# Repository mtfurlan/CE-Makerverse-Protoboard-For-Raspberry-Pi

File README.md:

# Protoboard For Raspberry Pi

Based on the one by CE, modified to include an eeprom from [Adafruit](https://github.com/adafruit/Adafruit-Perma-Proto-HAT-PCB) as example

Not finished, I got distracted and then stoppped needing this

## See also
* [RPI HAT spec](https://github.com/raspberrypi/utils/tree/master/eeptools)

## License
This project is open source - please review the LICENSE.md file for further licensing information.

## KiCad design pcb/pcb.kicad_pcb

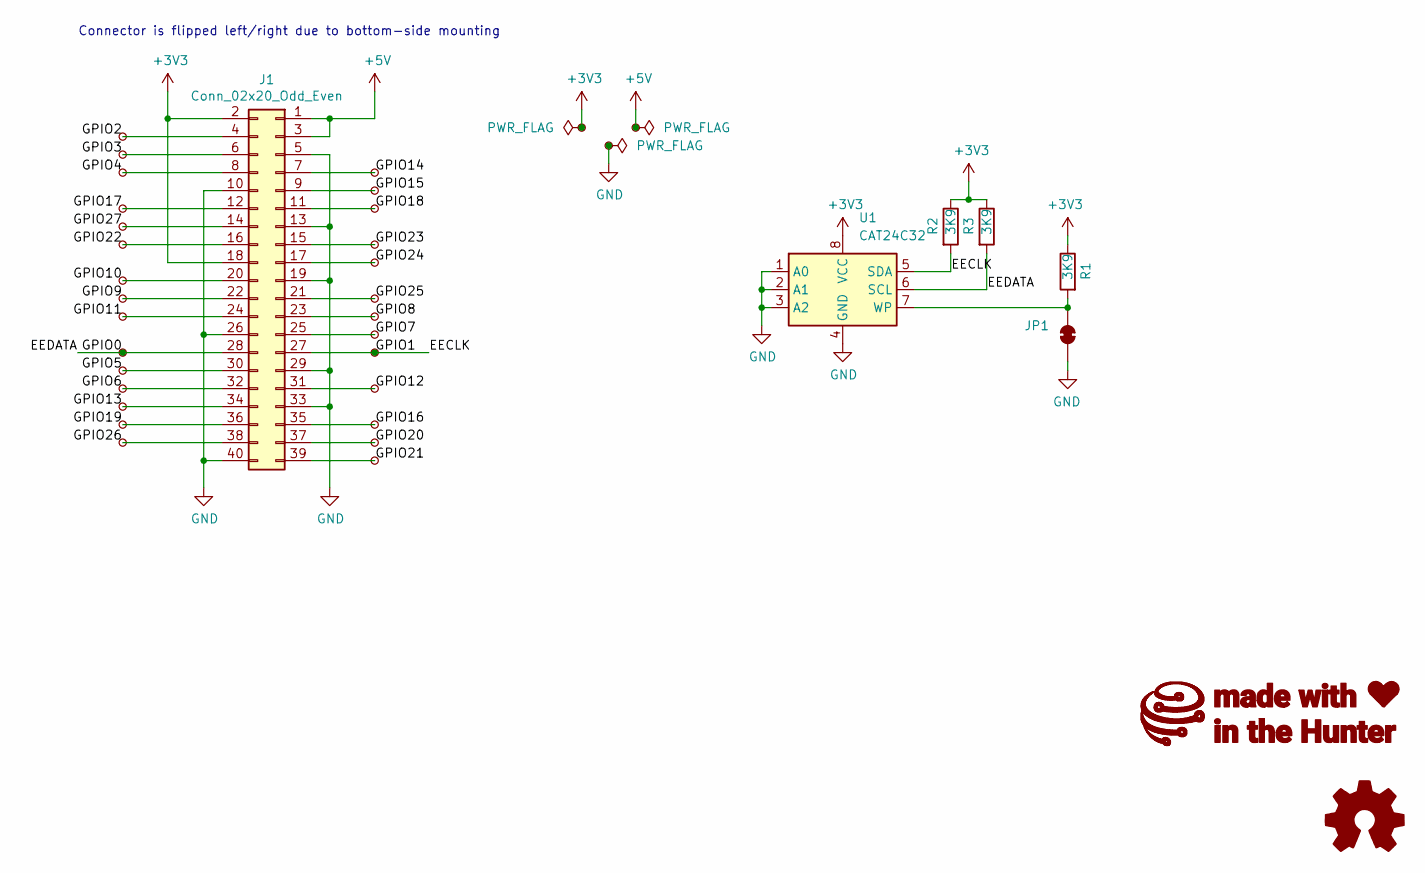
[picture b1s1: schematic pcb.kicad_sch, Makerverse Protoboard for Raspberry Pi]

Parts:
J1: Conn_02x20_Odd_Even; PinHeader_2x20_P2.54mm_Vertical
JP1: SolderJumper_2_Bridged; SolderJumper-2_P1.3mm_Bridged_RoundedPad1.0x1.5mm
LOGO1: Logo_Open_Hardware_Small; oshw
R1, R2, R3: 3K9; R_0603_1608Metric_Pad0.98x0.95mm_HandSolder
TP1, TP2, TP3, TP4, TP5, TP6, TP7, TP8, TP9, TP10, TP11, TP12, TP13, TP14, TP15, TP16, TP17, TP18, TP19, TP20, TP21, TP22, TP23, TP24, TP25, TP26, TP27, TP28: TestPoint_Small; 2-pin-row
TP29, TP31: TestPoint_Small; 4-pin-row
TP30: TestPoint_Small; BusRail-18-Hole
U1: CAT24C32; SOIC-8_3.9x4.9mm_P1.27mm

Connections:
+3V3: J1.2, J1.18, R1.1, R2.1, R3.1, TP29.1, U1.8 (VCC)
+5V: J1.1, J1.3, TP31.1
/EECLK: J1.27, R2.2, TP9.1, U1.5 (SDA)
/EEDATA: J1.28, R3.2, TP23.1, U1.6 (SCL)
/GPIO2: J1.4, TP14.1
/GPIO3: J1.6, TP15.1
/GPIO4: J1.8, TP16.1
/GPIO5: J1.30, TP24.1
/GPIO6: J1.32, TP25.1
/GPIO7: J1.25, TP8.1
/GPIO8: J1.23, TP7.1
/GPIO9: J1.22, TP21.1
/GPIO10: J1.20, TP20.1
/GPIO11: J1.24, TP22.1
/GPIO12: J1.31, TP10.1
/GPIO13: J1.34, TP26.1
/GPIO14: J1.7, TP1.1
/GPIO15: J1.9, TP2.1
/GPIO16: J1.35, TP11.1
/GPIO17: J1.12, TP17.1
/GPIO18: J1.11, TP3.1
/GPIO19: J1.36, TP27.1
/GPIO20: J1.37, TP12.1
/GPIO21: J1.39, TP13.1
/GPIO22: J1.16, TP19.1
/GPIO23: J1.15, TP4.1
/GPIO24: J1.17, TP5.1
/GPIO25: J1.21, TP6.1
/GPIO26: J1.38, TP28.1
/GPIO27: J1.14, TP18.1
GND: J1.5, J1.10, J1.13, J1.19, J1.26, J1.29, J1.33, J1.40, JP1.2 (B), TP30.1, U1.1 (A0), U1.2 (A1), U1.3 (A2), U1.4 (GND)
unnamed: JP1.1 (A), R1.2, U1.7 (WP)

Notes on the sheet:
Connector is flipped left/right due to bottom-side mounting

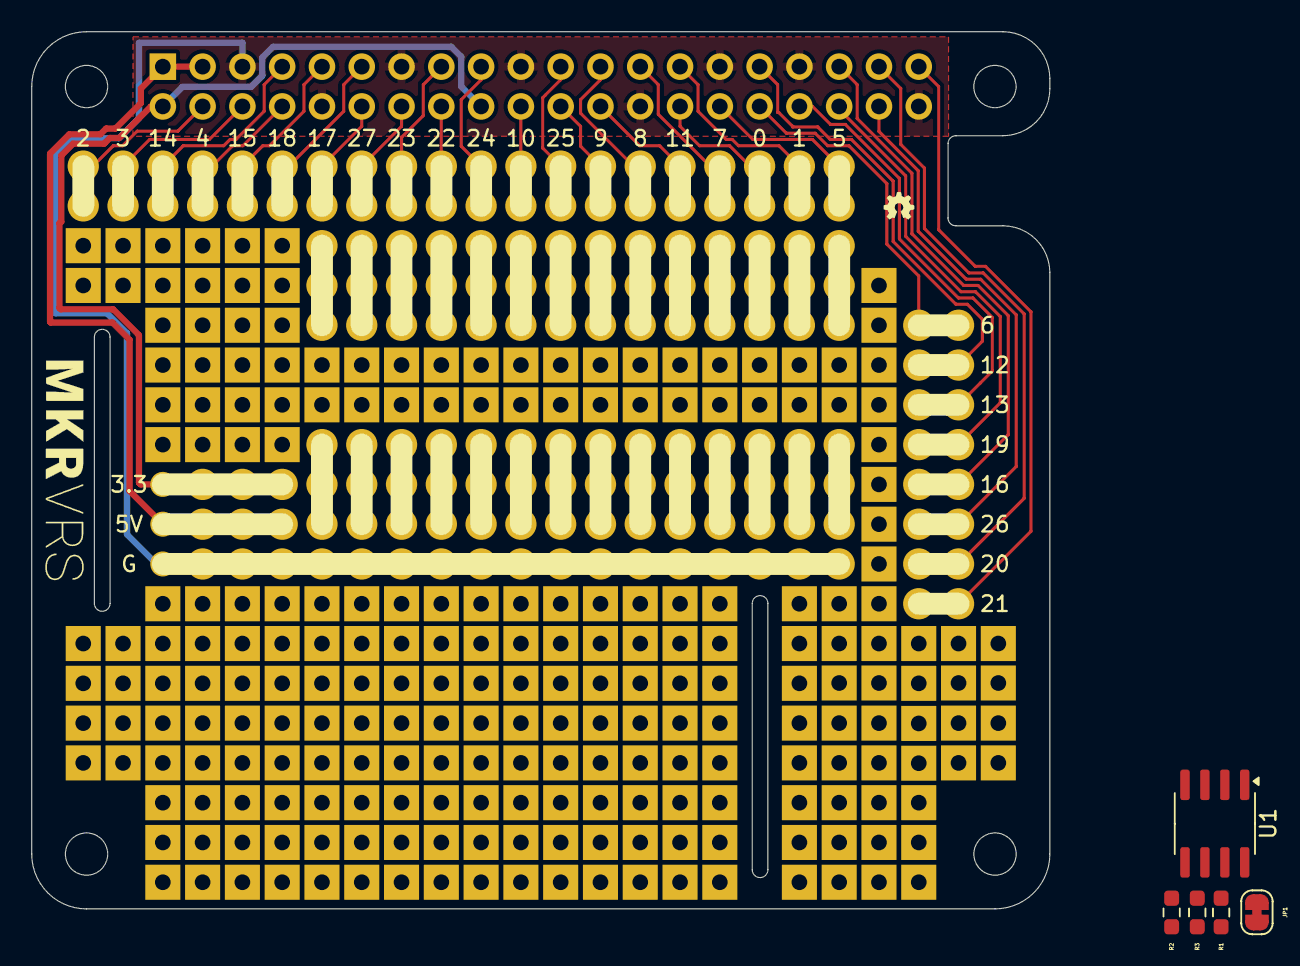
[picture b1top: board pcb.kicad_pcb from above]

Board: 2 copper layers, 65.0 x 56.0 mm, 42 parts (1 on the bottom side), 32 nets.

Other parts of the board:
H1, H2, H3, H4: MountingHole; MountingHole_2.7mm_M2.5

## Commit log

2022-12-05 v20 fix GPIO21 short to ground
2024-11-11 got schematic for eeprom in; no layout
2025-01-02 something
2025-01-02 not done sorry

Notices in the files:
pcb/pcb.kicad_pcb:
License: CCASAv4.0 https://creativecommons.org/licenses/by-sa/4.0
